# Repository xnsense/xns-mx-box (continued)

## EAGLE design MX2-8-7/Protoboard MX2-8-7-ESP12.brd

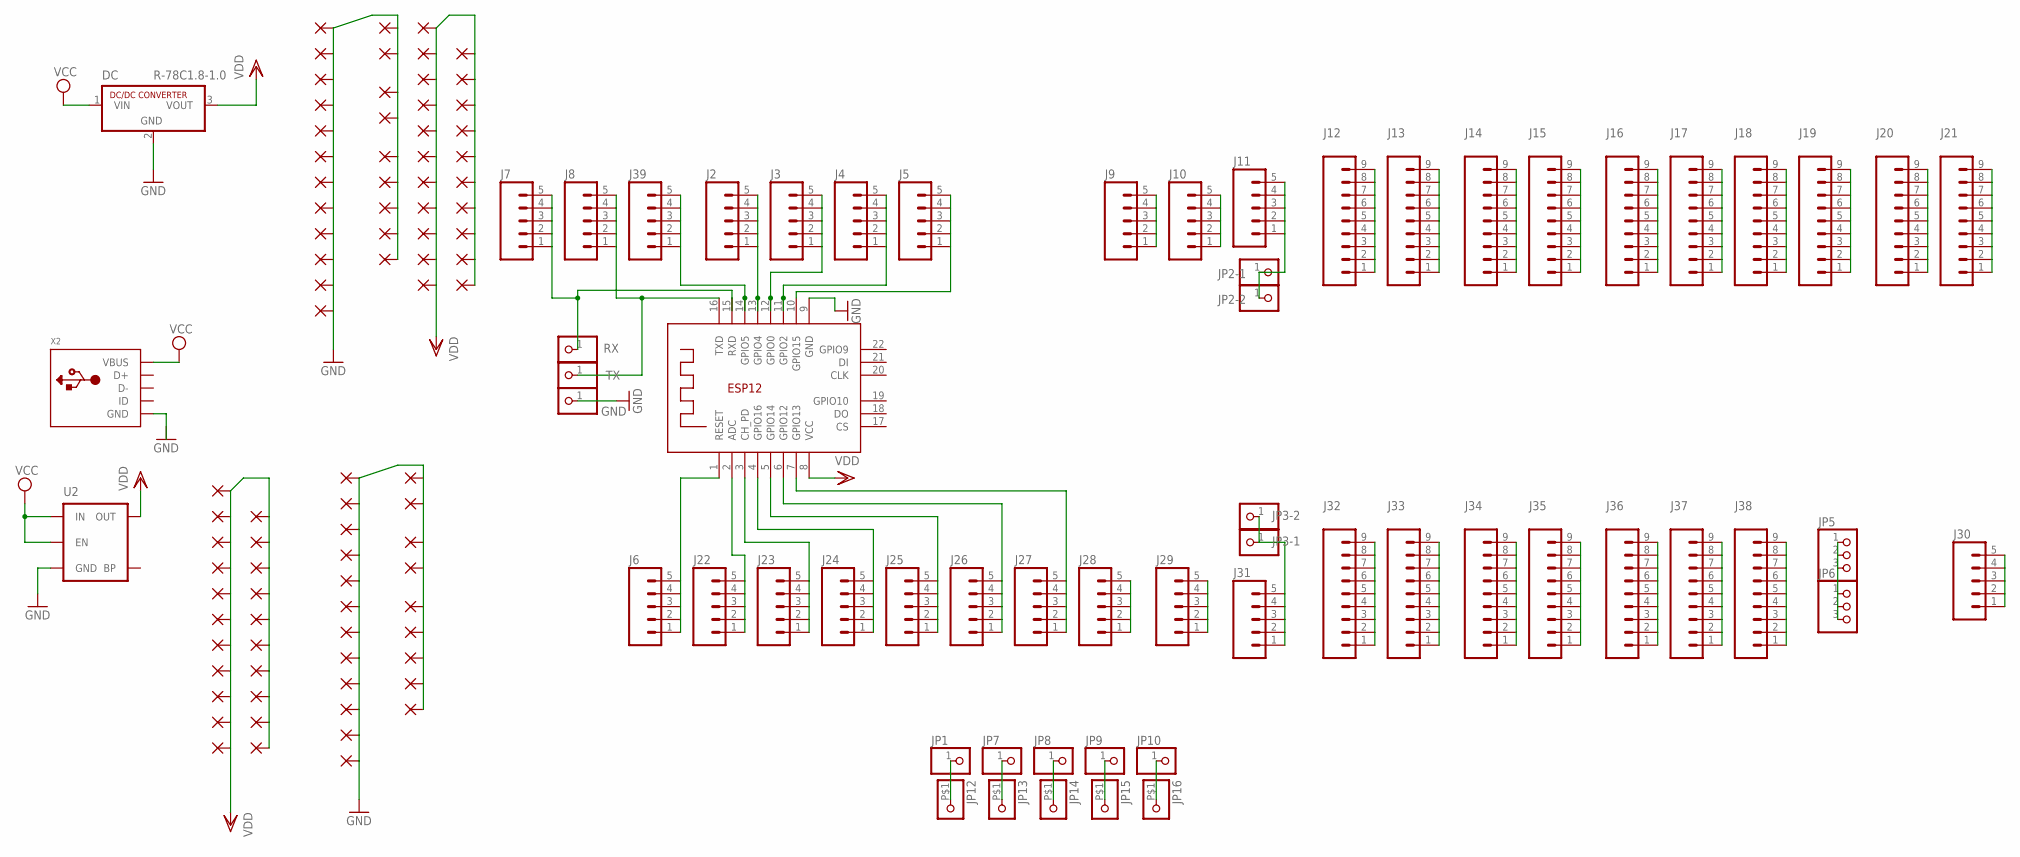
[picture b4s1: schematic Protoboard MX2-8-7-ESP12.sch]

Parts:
DC: R-78C1.8-1.0; SIP3
GND: PINHD-1X1CB; 1X01-CLEANBIG
J2, J3, J4, J5, J6, J7, J8, J9, J10, J11, J22, J23, J24, J25, J26, J27, J28, J29, J30, J31, J39: M05NO_SILK; 1X05_NO_SILK
J12, J13, J14, J15, J16, J17, J18, J19, J20, J21, J32, J33, J34, J35, J36, J37, J38: M09NO_SILK; 1X09_NO_SILK
JP1, JP2-1, JP2-2, JP3-1, JP3-2, JP7, JP8, JP9, JP10: PINHD-1X1CB; 1X01-CLEANBIG
JP5, JP6: PINHD-1X3CB; 1X03-CLEANBIG
JP12, JP13, JP14, JP15, JP16: PINHD-1X1-BIGPOGO; 1X1-BIGPOGO
PAD1, PAD2, PAD3, PAD4, PAD5, PAD6, PAD7, PAD8, PAD9, PAD10, PAD11, PAD12, PAD13, PAD14, PAD15, PAD16, PAD17, PAD18, PAD19, PAD22, PAD23, PAD24, PAD25, PAD26, PAD27, PAD28, PAD29, PAD30, PAD31, PAD32, PAD33, PAD34, PAD35, PAD36, PAD37, PAD39, PAD40, PAD41, PAD43, PAD44, PAD45, PAD46, PAD421, PAD422, PAD423, PAD424, PAD425, PAD426, PAD427, PAD428, PAD429, PAD430, PAD431, PAD432, PAD433, PAD434, PAD435, PAD436, PAD437, PAD438, PAD439, PAD440, PAD441, PAD442, PAD443, PAD444, PAD445, PAD446, PAD447, PAD448, PAD449, PAD450, PAD451, PAD452, PAD453, PAD454, PAD455, PAD456, PAD457, PAD458, PAD459, PAD460, PAD461, PAD462: 1,6/0,8
RX: PINHD-1X1CB; 1X01-CLEANBIG
TX: PINHD-1X1CB; 1X01-CLEANBIG
U2: MIC52053.3V; SOT23-5
X1: ESP-12E
X2: USB_MICRO_20329_V2; 4UCONN_20329_V2

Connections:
GND: DC.2 (GND), GND.1, PAD1.1, PAD2.1, PAD3.1, PAD4.1, PAD5.1, PAD6.1, PAD7.1, PAD8.1, PAD9.1, PAD10.1, PAD11.1, PAD12.1, PAD13.1, PAD14.1, PAD16.1, PAD17.1, PAD18.1, PAD19.1, PAD22.1, PAD23.1, PAD24.1, PAD421.1, PAD422.1, PAD423.1, PAD424.1, PAD425.1, PAD426.1, PAD427.1, PAD428.1, PAD429.1, PAD430.1, PAD431.1, PAD432.1, PAD433.1, PAD434.1, PAD435.1, PAD436.1, PAD437.1, PAD438.1, PAD439.1, PAD440.1, PAD441.1, U2.2 (GND), X1.9 (GND)
unnamed: J39.1, J39.2, J39.3, J39.4, J39.5, X1.14 (GPIO5)
unnamed: JP1.1, JP12.P$1
unnamed: J2.1, J2.2, J2.3, J2.4, J2.5, X1.13 (GPIO4)
unnamed: J3.1, J3.2, J3.3, J3.4, J3.5, X1.12 (GPIO0)
unnamed: J4.1, J4.2, J4.3, J4.4, J4.5, X1.11 (GPIO2)
unnamed: J5.1, J5.2, J5.3, J5.4, J5.5, X1.10 (GPIO15)
unnamed: J9.1, J9.2, J9.3, J9.4, J9.5
unnamed: J10.1, J10.2, J10.3, J10.4, J10.5
unnamed: J11.1, J11.2, J11.3, J11.4, J11.5, JP2-1.1, JP2-2.1
unnamed: J12.1, J12.2, J12.3, J12.4, J12.5, J12.6, J12.7, J12.8, J12.9
unnamed: J13.1, J13.2, J13.3, J13.4, J13.5, J13.6, J13.7, J13.8, J13.9
unnamed: J14.1, J14.2, J14.3, J14.4, J14.5, J14.6, J14.7, J14.8, J14.9
unnamed: J15.1, J15.2, J15.3, J15.4, J15.5, J15.6, J15.7, J15.8, J15.9
unnamed: J16.1, J16.2, J16.3, J16.4, J16.5, J16.6, J16.7, J16.8, J16.9
unnamed: J17.1, J17.2, J17.3, J17.4, J17.5, J17.6, J17.7, J17.8, J17.9
unnamed: J18.1, J18.2, J18.3, J18.4, J18.5, J18.6, J18.7, J18.8, J18.9
unnamed: J19.1, J19.2, J19.3, J19.4, J19.5, J19.6, J19.7, J19.8, J19.9
unnamed: J20.1, J20.2, J20.3, J20.4, J20.5, J20.6, J20.7, J20.8, J20.9
unnamed: J21.1, J21.2, J21.3, J21.4, J21.5, J21.6, J21.7, J21.8, J21.9
unnamed: J6.1, J6.2, J6.3, J6.4, J6.5, X1.1 (RESET)
unnamed: J22.1, J22.2, J22.3, J22.4, J22.5, X1.2 (ADC)
unnamed: J23.1, J23.2, J23.3, J23.4, J23.5, X1.3 (CH_PD)
unnamed: J24.1, J24.2, J24.3, J24.4, J24.5, X1.4 (GPIO16)
unnamed: J25.1, J25.2, J25.3, J25.4, J25.5, X1.5 (GPIO14)
unnamed: J26.1, J26.2, J26.3, J26.4, J26.5, X1.6 (GPIO12)
unnamed: J27.1, J27.2, J27.3, J27.4, J27.5, X1.7 (GPIO13)
unnamed: J28.1, J28.2, J28.3, J28.4, J28.5
unnamed: J29.1, J29.2, J29.3, J29.4, J29.5
unnamed: J31.1, J31.2, J31.3, J31.4, J31.5, JP3-1.1, JP3-2.1
unnamed: J32.1, J32.2, J32.3, J32.4, J32.5, J32.6, J32.7, J32.8, J32.9
unnamed: J33.1, J33.2, J33.3, J33.4, J33.5, J33.6, J33.7, J33.8, J33.9
unnamed: JP7.1, JP13.P$1
unnamed: J34.1, J34.2, J34.3, J34.4, J34.5, J34.6, J34.7, J34.8, J34.9
unnamed: J35.1, J35.2, J35.3, J35.4, J35.5, J35.6, J35.7, J35.8, J35.9
unnamed: J36.1, J36.2, J36.3, J36.4, J36.5, J36.6, J36.7, J36.8, J36.9
unnamed: J37.1, J37.2, J37.3, J37.4, J37.5, J37.6, J37.7, J37.8, J37.9
unnamed: J38.1, J38.2, J38.3, J38.4, J38.5, J38.6, J38.7, J38.8, J38.9
unnamed: JP5.1, JP5.2, JP5.3, JP6.1, JP6.2, JP6.3
unnamed: J30.1, J30.2, J30.3, J30.4, J30.5
unnamed: JP8.1, JP14.P$1
unnamed: JP9.1, JP15.P$1
unnamed: JP10.1, JP16.P$1
unnamed: J7.1, J7.2, J7.3, J7.4, J7.5, RX.1, X1.15 (RXD)
unnamed: J8.1, J8.2, J8.3, J8.4, J8.5, TX.1, X1.16 (TXD)
unnamed: X2.BASE@1 (GND), X2.BASE@2 (GND), X2.GND, X2.SPRT@1 (GND), X2.SPRT@2 (GND), X2.SPRT@3 (GND), X2.SPRT@4 (GND)
VCC: DC.1 (VIN), U2.1 (IN), U2.3 (EN), X2.VBUS
VDD: DC.3 (VOUT), PAD15.1, PAD25.1, PAD26.1, PAD27.1, PAD28.1, PAD29.1, PAD30.1, PAD31.1, PAD32.1, PAD33.1, PAD34.1, PAD35.1, PAD36.1, PAD37.1, PAD39.1, PAD40.1, PAD41.1, PAD43.1, PAD44.1, PAD45.1, PAD46.1, PAD442.1, PAD443.1, PAD444.1, PAD445.1, PAD446.1, PAD447.1, PAD448.1, PAD449.1, PAD450.1, PAD451.1, PAD452.1, PAD453.1, PAD454.1, PAD455.1, PAD456.1, PAD457.1, PAD458.1, PAD459.1, PAD460.1, PAD461.1, PAD462.1, U2.5 (OUT), X1.8 (VCC)

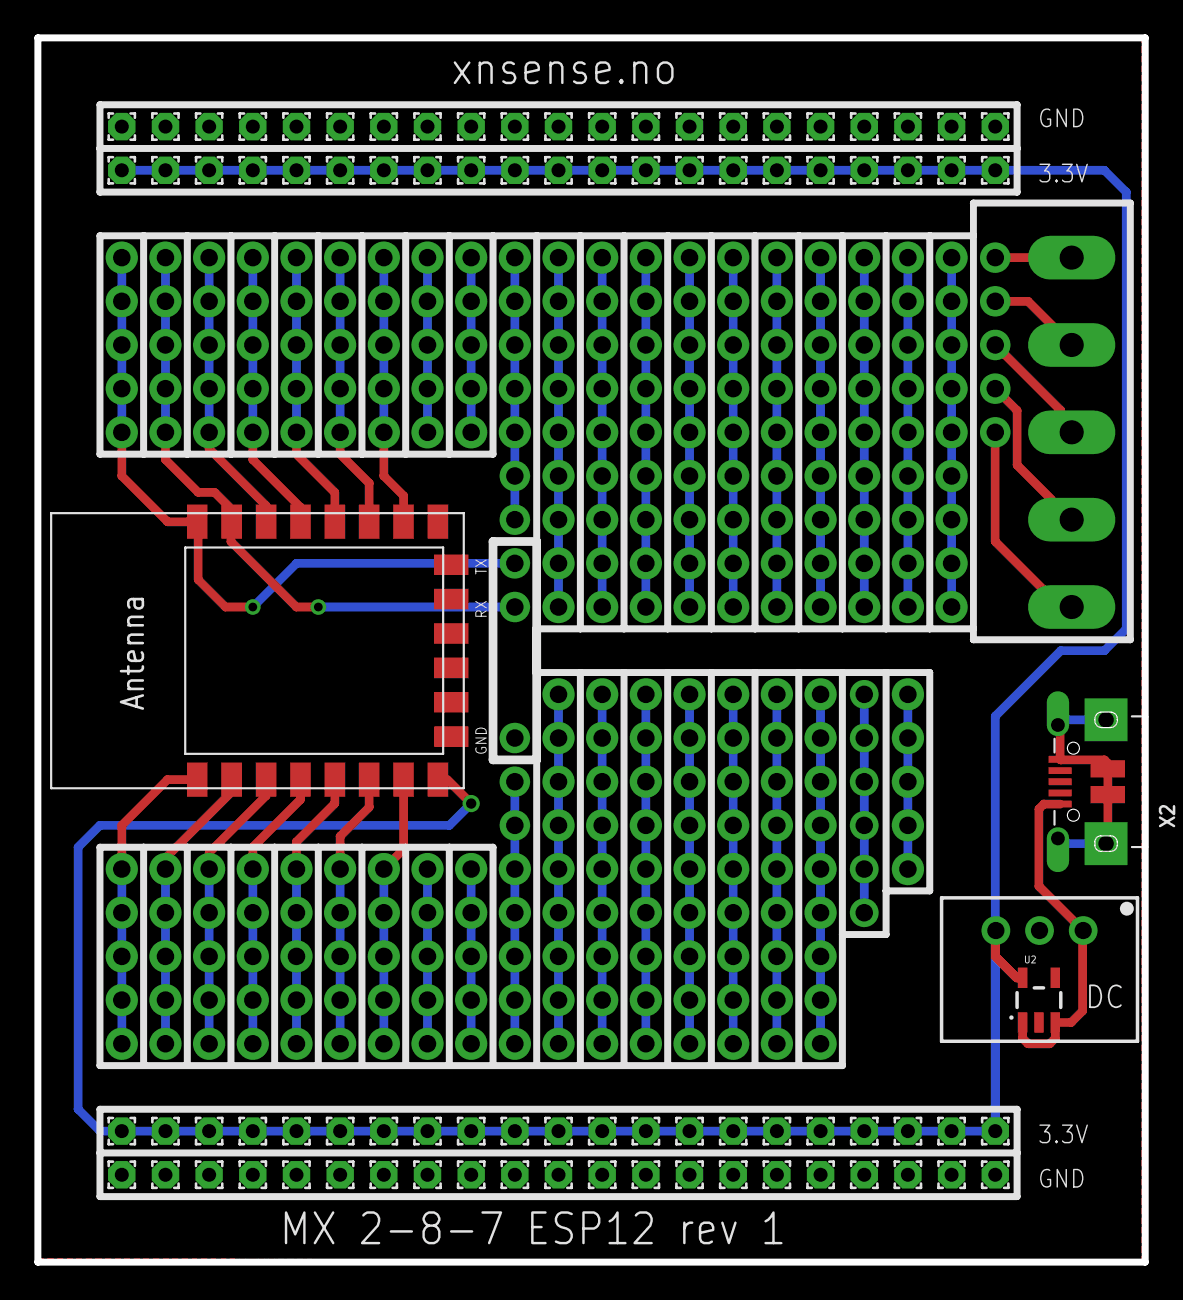
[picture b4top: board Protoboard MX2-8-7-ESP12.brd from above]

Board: 2 copper layers, 64.4 x 71.2 mm, 145 parts (0 on the bottom side), 48 nets.

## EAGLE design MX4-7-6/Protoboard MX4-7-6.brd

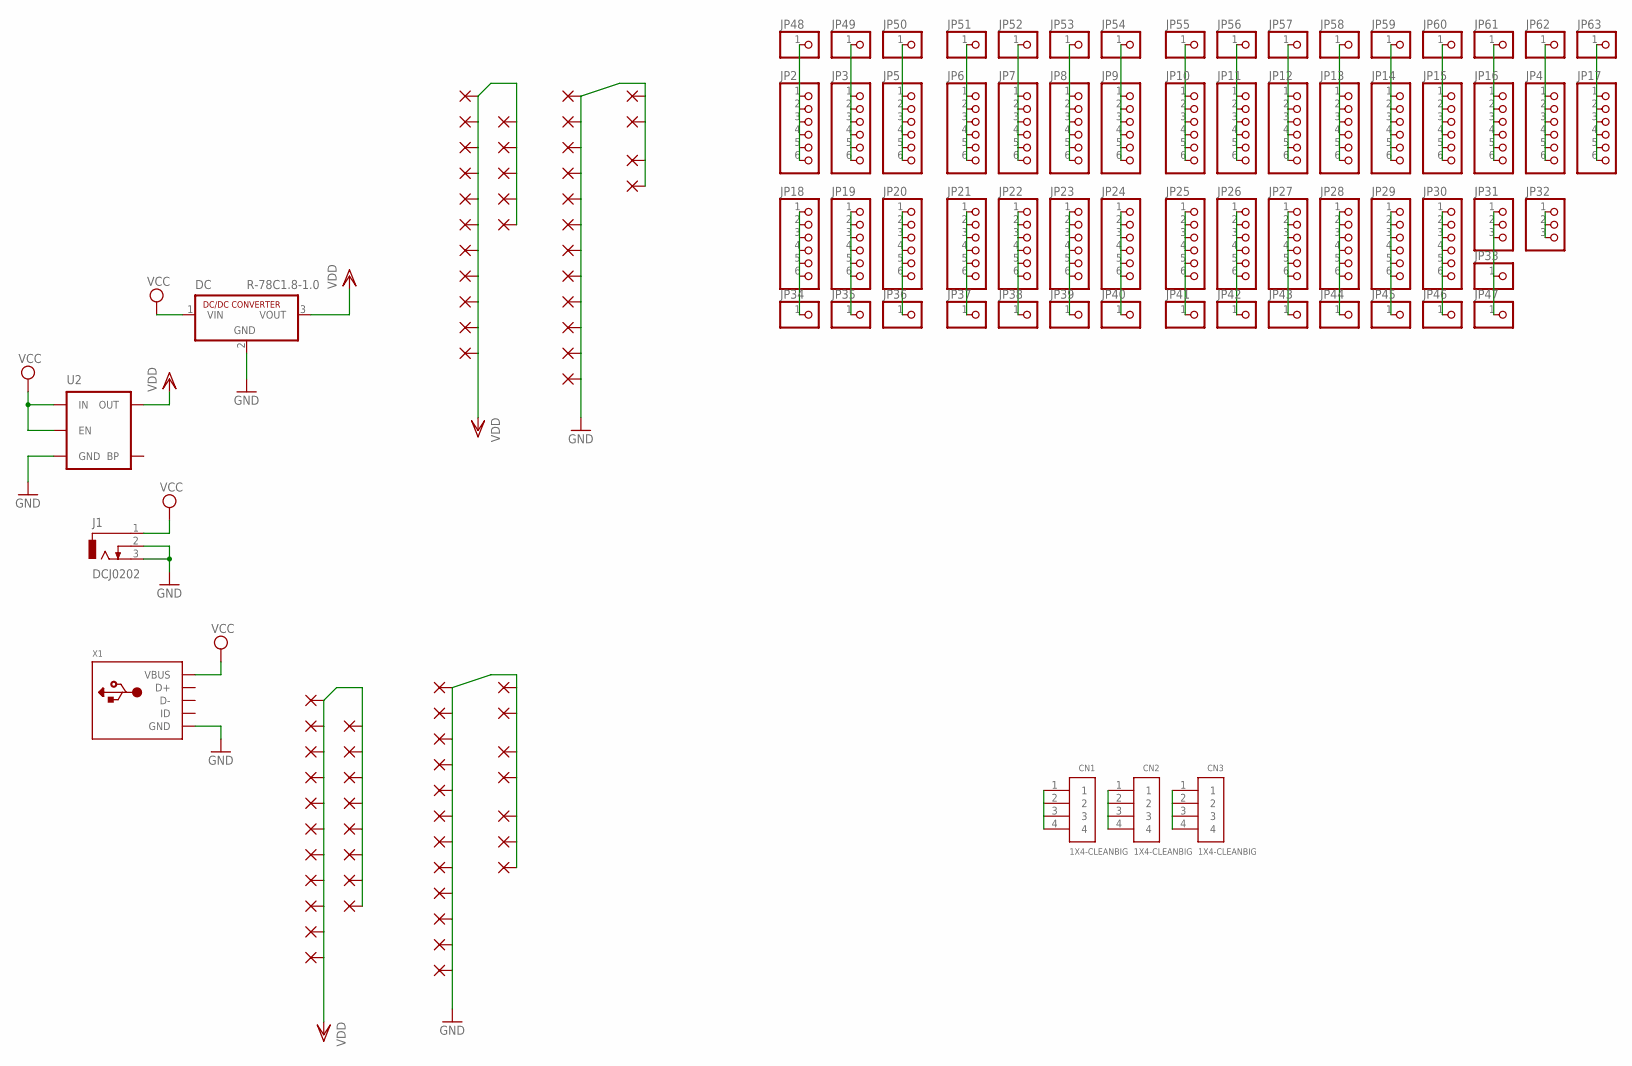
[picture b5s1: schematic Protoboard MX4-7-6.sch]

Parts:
CN1, CN2, CN3: 1X4-CLEANBIG; 1X04-CLEANBIG
DC: R-78C1.8-1.0; SIP3
J1: DCJ0202
JP2, JP3, JP4, JP5, JP6, JP7, JP8, JP9, JP10, JP11, JP12, JP13, JP14, JP15, JP16, JP17, JP18, JP19, JP20, JP21, JP22, JP23, JP24, JP25, JP26, JP27, JP28, JP29, JP30: PINHD-1X6CB; 1X06-CLEANBIG
JP31, JP32: PINHD-1X3CB; 1X03-CLEANBIG
JP33, JP34, JP35, JP36, JP37, JP38, JP39, JP40, JP41, JP42, JP43, JP44, JP45, JP46, JP47, JP48, JP49, JP50, JP51, JP52, JP53, JP54, JP55, JP56, JP57, JP58, JP59, JP60, JP61, JP62, JP63: PINHD-1X1CB; 1X01-CLEANBIG
PAD4, PAD5, PAD6, PAD7, PAD8, PAD9, PAD10, PAD11, PAD12, PAD13, PAD14, PAD15, PAD16, PAD17, PAD18, PAD19, PAD20, PAD21, PAD22, PAD23, PAD24, PAD25, PAD26, PAD27, PAD28, PAD29, PAD30, PAD31, PAD32, PAD33, PAD36, PAD38, PAD421, PAD422, PAD423, PAD424, PAD425, PAD426, PAD427, PAD428, PAD429, PAD430, PAD431, PAD432, PAD433, PAD434, PAD435, PAD436, PAD439, PAD440, PAD441, PAD442, PAD443, PAD444, PAD445, PAD446, PAD447, PAD448, PAD449, PAD450, PAD451, PAD452, PAD453, PAD454, PAD455, PAD456, PAD459, PAD460, PAD461, PAD462: 1,6/0,8
U2: MIC52053.3V; SOT23-5
X1: USBMICRO_20329; 4UCONN_20329

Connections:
GND: DC.2 (GND), J1.2, J1.3, PAD4.1, PAD17.1, PAD22.1, PAD23.1, PAD24.1, PAD25.1, PAD26.1, PAD27.1, PAD28.1, PAD29.1, PAD30.1, PAD31.1, PAD32.1, PAD33.1, PAD36.1, PAD38.1, PAD421.1, PAD422.1, PAD423.1, PAD424.1, PAD425.1, PAD426.1, PAD427.1, PAD428.1, PAD429.1, PAD430.1, PAD431.1, PAD432.1, PAD433.1, PAD434.1, PAD435.1, PAD436.1, PAD439.1, PAD440.1, PAD441.1, U2.2 (GND), X1.BASE@1 (GND), X1.BASE@2 (GND), X1.GND, X1.SPRT@1 (GND), X1.SPRT@2 (GND), X1.SPRT@3 (GND), X1.SPRT@4 (GND)
unnamed: JP2.1, JP2.2, JP2.3, JP2.4, JP2.5, JP2.6, JP48.1
unnamed: CN1.1, CN1.2, CN1.3, CN1.4
unnamed: CN2.1, CN2.2, CN2.3, CN2.4
unnamed: CN3.1, CN3.2, CN3.3, CN3.4
unnamed: JP3.1, JP3.2, JP3.3, JP3.4, JP3.5, JP3.6, JP49.1
unnamed: JP5.1, JP5.2, JP5.3, JP5.4, JP5.5, JP5.6, JP50.1
unnamed: JP6.1, JP6.2, JP6.3, JP6.4, JP6.5, JP6.6, JP51.1
unnamed: JP7.1, JP7.2, JP7.3, JP7.4, JP7.5, JP7.6, JP52.1
unnamed: JP8.1, JP8.2, JP8.3, JP8.4, JP8.5, JP8.6, JP53.1
unnamed: JP9.1, JP9.2, JP9.3, JP9.4, JP9.5, JP9.6, JP54.1
unnamed: JP10.1, JP10.2, JP10.3, JP10.4, JP10.5, JP10.6, JP55.1
unnamed: JP11.1, JP11.2, JP11.3, JP11.4, JP11.5, JP11.6, JP56.1
unnamed: JP12.1, JP12.2, JP12.3, JP12.4, JP12.5, JP12.6, JP57.1
unnamed: JP13.1, JP13.2, JP13.3, JP13.4, JP13.5, JP13.6, JP58.1
unnamed: JP14.1, JP14.2, JP14.3, JP14.4, JP14.5, JP14.6, JP59.1
unnamed: JP15.1, JP15.2, JP15.3, JP15.4, JP15.5, JP15.6, JP60.1
unnamed: JP16.1, JP16.2, JP16.3, JP16.4, JP16.5, JP16.6, JP61.1
unnamed: JP4.1, JP4.2, JP4.3, JP4.4, JP4.5, JP4.6, JP62.1
unnamed: JP17.1, JP17.2, JP17.3, JP17.4, JP17.5, JP17.6, JP63.1
unnamed: JP18.1, JP18.2, JP18.3, JP18.4, JP18.5, JP18.6, JP34.1
unnamed: JP19.1, JP19.2, JP19.3, JP19.4, JP19.5, JP19.6, JP35.1
unnamed: JP20.1, JP20.2, JP20.3, JP20.4, JP20.5, JP20.6, JP36.1
unnamed: JP21.1, JP21.2, JP21.3, JP21.4, JP21.5, JP21.6, JP37.1
unnamed: JP22.1, JP22.2, JP22.3, JP22.4, JP22.5, JP22.6, JP38.1
unnamed: JP23.1, JP23.2, JP23.3, JP23.4, JP23.5, JP23.6, JP39.1
unnamed: JP24.1, JP24.2, JP24.3, JP24.4, JP24.5, JP24.6, JP40.1
unnamed: JP25.1, JP25.2, JP25.3, JP25.4, JP25.5, JP25.6, JP41.1
unnamed: JP26.1, JP26.2, JP26.3, JP26.4, JP26.5, JP26.6, JP42.1
unnamed: JP27.1, JP27.2, JP27.3, JP27.4, JP27.5, JP27.6, JP43.1
unnamed: JP28.1, JP28.2, JP28.3, JP28.4, JP28.5, JP28.6, JP44.1
unnamed: JP29.1, JP29.2, JP29.3, JP29.4, JP29.5, JP29.6, JP45.1
unnamed: JP30.1, JP30.2, JP30.3, JP30.4, JP30.5, JP30.6, JP46.1
unnamed: JP31.1, JP31.2, JP31.3, JP33.1, JP47.1
unnamed: JP32.1, JP32.2, JP32.3
VCC: DC.1 (VIN), J1.1, U2.1 (IN), U2.3 (EN), X1.VBUS
VDD: DC.3 (VOUT), PAD5.1, PAD6.1, PAD7.1, PAD8.1, PAD9.1, PAD10.1, PAD11.1, PAD12.1, PAD13.1, PAD14.1, PAD15.1, PAD16.1, PAD18.1, PAD19.1, PAD20.1, PAD21.1, PAD442.1, PAD443.1, PAD444.1, PAD445.1, PAD446.1, PAD447.1, PAD448.1, PAD449.1, PAD450.1, PAD451.1, PAD452.1, PAD453.1, PAD454.1, PAD455.1, PAD456.1, PAD459.1, PAD460.1, PAD461.1, PAD462.1, U2.5 (OUT)

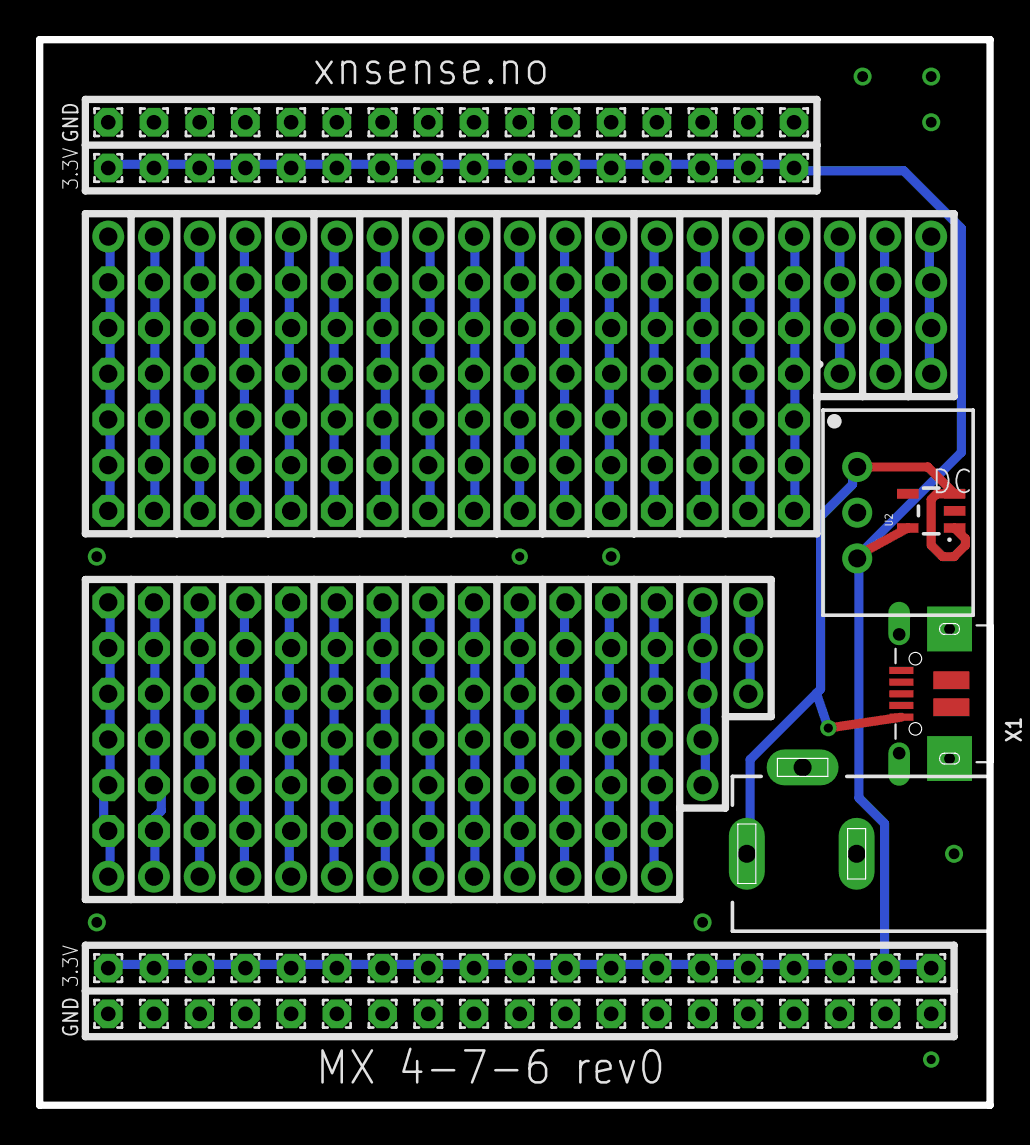
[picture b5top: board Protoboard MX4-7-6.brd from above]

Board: 2 copper layers, 52.8 x 59.2 mm, 139 parts (0 on the bottom side), 37 nets.

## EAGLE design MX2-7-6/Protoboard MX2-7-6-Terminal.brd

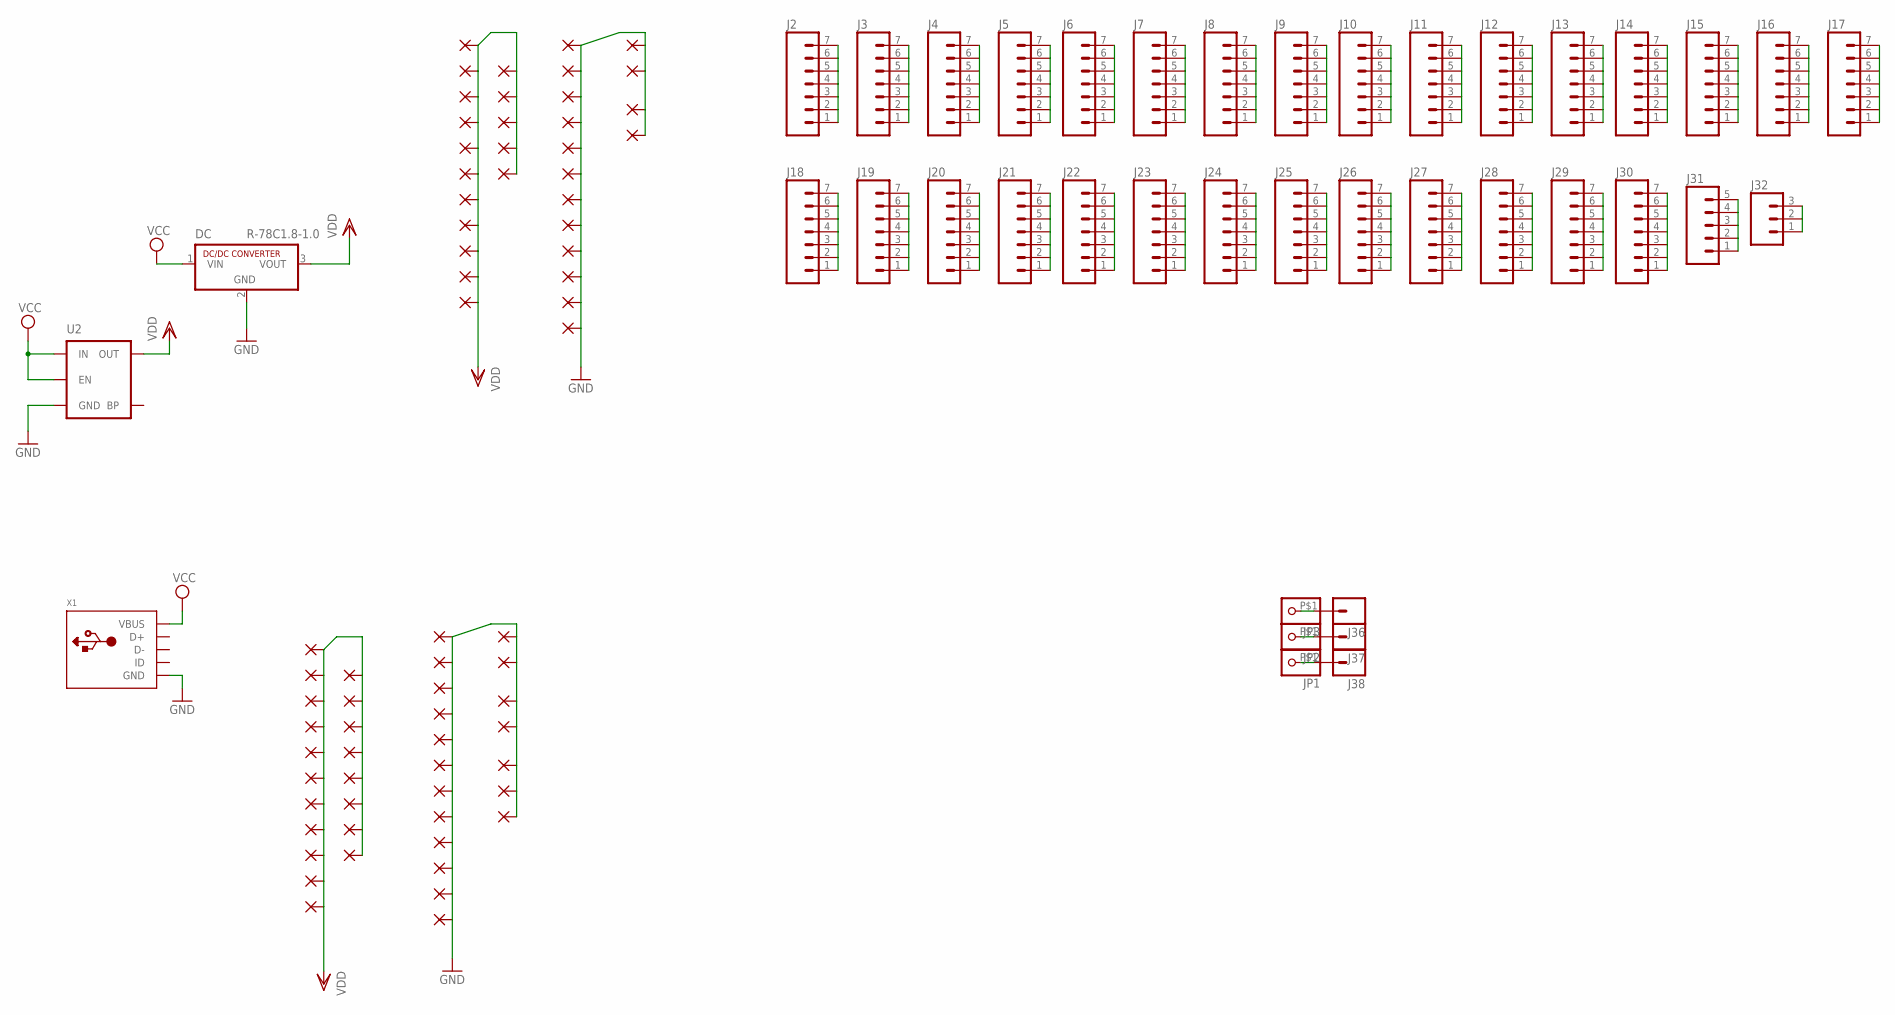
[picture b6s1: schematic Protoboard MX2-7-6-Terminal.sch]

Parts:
DC: R-78C1.8-1.0; SIP3
J2, J3, J4, J5, J6, J7, J8, J9, J10, J11, J12, J13, J14, J15, J16, J17, J18, J19, J20, J21, J22, J23, J24, J25, J26, J27, J28, J29, J30: M07NO_SILK; 1X07_NO_SILK
J31: M05NO_SILK; 1X05_NO_SILK
J32: M031X03_NO_SILK; 1X03_NO_SILK
J36, J37, J38: M01PTH_NO_SILK_YES_STOP; 1X01_NO_SILK
JP1, JP2, JP3: PINHD-1X1-BIGPOGO; 1X1-BIGPOGO
PAD4, PAD5, PAD6, PAD7, PAD8, PAD9, PAD10, PAD11, PAD12, PAD13, PAD14, PAD15, PAD16, PAD17, PAD18, PAD19, PAD20, PAD21, PAD22, PAD23, PAD24, PAD25, PAD26, PAD27, PAD28, PAD29, PAD30, PAD31, PAD32, PAD33, PAD36, PAD38, PAD421, PAD422, PAD423, PAD424, PAD425, PAD426, PAD427, PAD428, PAD429, PAD430, PAD431, PAD432, PAD433, PAD434, PAD435, PAD436, PAD439, PAD440, PAD441, PAD442, PAD443, PAD444, PAD445, PAD446, PAD447, PAD448, PAD449, PAD450, PAD451, PAD452, PAD453, PAD454, PAD455, PAD456, PAD459, PAD460, PAD461, PAD462: 1,6/0,8
U2: MIC52053.3V; SOT23-5
X1: USBMICRO_20329; 4UCONN_20329

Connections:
GND: DC.2 (GND), PAD4.1, PAD17.1, PAD22.1, PAD23.1, PAD24.1, PAD25.1, PAD26.1, PAD27.1, PAD28.1, PAD29.1, PAD30.1, PAD31.1, PAD32.1, PAD33.1, PAD36.1, PAD38.1, PAD421.1, PAD422.1, PAD423.1, PAD424.1, PAD425.1, PAD426.1, PAD427.1, PAD428.1, PAD429.1, PAD430.1, PAD431.1, PAD432.1, PAD433.1, PAD434.1, PAD435.1, PAD436.1, PAD439.1, PAD440.1, PAD441.1, U2.2 (GND), X1.BASE@1 (GND), X1.BASE@2 (GND), X1.GND, X1.SPRT@1 (GND), X1.SPRT@2 (GND), X1.SPRT@3 (GND), X1.SPRT@4 (GND)
unnamed: J2.1, J2.2, J2.3, J2.4, J2.5, J2.6, J2.7
unnamed: J36.1, JP3.P$1
unnamed: J37.1, JP2.P$1
unnamed: J38.1, JP1.P$1
unnamed: J3.1, J3.2, J3.3, J3.4, J3.5, J3.6, J3.7
unnamed: J4.1, J4.2, J4.3, J4.4, J4.5, J4.6, J4.7
unnamed: J5.1, J5.2, J5.3, J5.4, J5.5, J5.6, J5.7
unnamed: J6.1, J6.2, J6.3, J6.4, J6.5, J6.6, J6.7
unnamed: J7.1, J7.2, J7.3, J7.4, J7.5, J7.6, J7.7
unnamed: J8.1, J8.2, J8.3, J8.4, J8.5, J8.6, J8.7
unnamed: J9.1, J9.2, J9.3, J9.4, J9.5, J9.6, J9.7
unnamed: J10.1, J10.2, J10.3, J10.4, J10.5, J10.6, J10.7
unnamed: J11.1, J11.2, J11.3, J11.4, J11.5, J11.6, J11.7
unnamed: J12.1, J12.2, J12.3, J12.4, J12.5, J12.6, J12.7
unnamed: J13.1, J13.2, J13.3, J13.4, J13.5, J13.6, J13.7
unnamed: J14.1, J14.2, J14.3, J14.4, J14.5, J14.6, J14.7
unnamed: J15.1, J15.2, J15.3, J15.4, J15.5, J15.6, J15.7
unnamed: J16.1, J16.2, J16.3, J16.4, J16.5, J16.6, J16.7
unnamed: J17.1, J17.2, J17.3, J17.4, J17.5, J17.6, J17.7
unnamed: J18.1, J18.2, J18.3, J18.4, J18.5, J18.6, J18.7
unnamed: J19.1, J19.2, J19.3, J19.4, J19.5, J19.6, J19.7
unnamed: J20.1, J20.2, J20.3, J20.4, J20.5, J20.6, J20.7
unnamed: J21.1, J21.2, J21.3, J21.4, J21.5, J21.6, J21.7
unnamed: J22.1, J22.2, J22.3, J22.4, J22.5, J22.6, J22.7
unnamed: J23.1, J23.2, J23.3, J23.4, J23.5, J23.6, J23.7
unnamed: J24.1, J24.2, J24.3, J24.4, J24.5, J24.6, J24.7
unnamed: J25.1, J25.2, J25.3, J25.4, J25.5, J25.6, J25.7
unnamed: J26.1, J26.2, J26.3, J26.4, J26.5, J26.6, J26.7
unnamed: J27.1, J27.2, J27.3, J27.4, J27.5, J27.6, J27.7
unnamed: J28.1, J28.2, J28.3, J28.4, J28.5, J28.6, J28.7
unnamed: J29.1, J29.2, J29.3, J29.4, J29.5, J29.6, J29.7
unnamed: J30.1, J30.2, J30.3, J30.4, J30.5, J30.6, J30.7
unnamed: J31.1, J31.2, J31.3, J31.4, J31.5
unnamed: J32.1, J32.2, J32.3
VCC: DC.1 (VIN), U2.1 (IN), U2.3 (EN), X1.VBUS
VDD: DC.3 (VOUT), PAD5.1, PAD6.1, PAD7.1, PAD8.1, PAD9.1, PAD10.1, PAD11.1, PAD12.1, PAD13.1, PAD14.1, PAD15.1, PAD16.1, PAD18.1, PAD19.1, PAD20.1, PAD21.1, PAD442.1, PAD443.1, PAD444.1, PAD445.1, PAD446.1, PAD447.1, PAD448.1, PAD449.1, PAD450.1, PAD451.1, PAD452.1, PAD453.1, PAD454.1, PAD455.1, PAD456.1, PAD459.1, PAD460.1, PAD461.1, PAD462.1, U2.5 (OUT)

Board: 2 copper layers, 110 parts (0 on the bottom side), 37 nets, no tracks yet.

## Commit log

2016-11-16 Init
    First Commit
2016-11-18 Gerb. files
    Created Gerb files
2016-11-21 Gerb files
    Added herb files
2016-11-22 Created ESP12 versions
2016-11-22 Gerb files
    Gerb files for MX-3-11-8
2016-11-24 Moved RJ45
    Moved RJ45 a bit into the board and created new Gerb files to factory
2016-11-26 Moved RJ45 5mil to the left, to align it's outline to board outline
2016-11-26 New Gerb after RJ45 move
    New Gerb after RJ45 move
2016-12-05 Adjusted Polygon
    Adjusted Polygon on all boxes. Changed length on MX-4-7-6 to fit the
    box, it was 2mm to long.
2016-12-16 Update Gerb files
    Created Gerber files for MX 2-7-6 without ESP
2017-01-08 Update to rev2
    Updated to Pin headers instead of single wire pads
2017-01-08 Change usb connector
    Change to correct usb connecter and moved esp8266 bit more onto the
    board.
2017-01-08 Change ESP Module
    Changed to Device/Package Adafruit uses
2017-01-09 Update esp component and usb
    test
2017-01-09 update and and 3.3V label
    Update labels
2017-01-09 Routed
2017-01-09 Revert "Routed"
    This reverts commit bd5565199344e69dd12e80519bf5855103d987e6.
2017-01-09 Revert "Routed"
    This reverts commit 078e80659a45ef39a7709107a01737087c5908e1.
2017-01-09 Routed and Gerb files
    Routed and produced gerb files
2017-01-09 Fixed revert and sccidental deletion
2017-01-10 Remove ignore zip files
2017-01-10 Gerb files added
    Added Gerb files
2017-01-10 Routing and Gerber files
    Routed and produced gerber files
2017-01-10 Crossing lines with 3.3V
2017-01-20 Silkscreen text fixes
    Silkscreen text fixes
